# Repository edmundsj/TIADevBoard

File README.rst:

+/-5V TIA Dev Board
=========================

Features
----------
- On-board +/-5V supply generation
- Uses a low-noise opamp: ADA4622 (<1fA/rtHz, <15nV/rtHz)
- Low bias current opamp (<10pA) for accurate DC current measurement
- Opamp is unity gain stable, no input offset (<2uV), common-mode input beyond the rails, R2R output
- SMA input and output
- Low parasitic input/output capacitance

Issues in Versions 1,2
-----------------------
- [FIXED in v3] Old versions of this PCB relied on an off-board +/-15V dual supply, which was coupling in a huge amount of noise into the opamp.
- [FIXED in v3] Old opamp (ADA4625) appears to be often out of stock and is quite expensive (~$10). 

Issues in Version 3
--------------------
- The screw terminal is exerting force on an unspported area of the PCB, I should add another couple of standoffs so this does not happen.
- The -5V input is actually -7.5V. Should use two 3k resistors instead of two 1k resistors
- [FIXED v4] Pin 2 (sense pin) on ADP7183 is not connected to anything. It should be connected to Vout.
- [FIXED v4] There should be a 1uF capacitor to ground hanging off pin VA.
- [FIXED v4] There should be a 10nF capacitor between VA and VFB, not 1uF.

Issues in Version 4
---------------------
- [FIXED v5] Very high output noise (~10uV/rtHz) when driving diode with opamp. Switched to driving with GND.
- [FIXED v5] OPA2387 appears to have ~5x the specced current noise. Switched to ADA4622 (0.7fA/rtHz vs 70). 
- [FIXED v5] Switch back to dual supply with linear regulators
- [FIXED v5] Filter the output of the switched supply with an CLC network
- [FIXED v5] Add bulkhead-mount input/output SMA connectors to enclose entire board in grounded Faraday cage

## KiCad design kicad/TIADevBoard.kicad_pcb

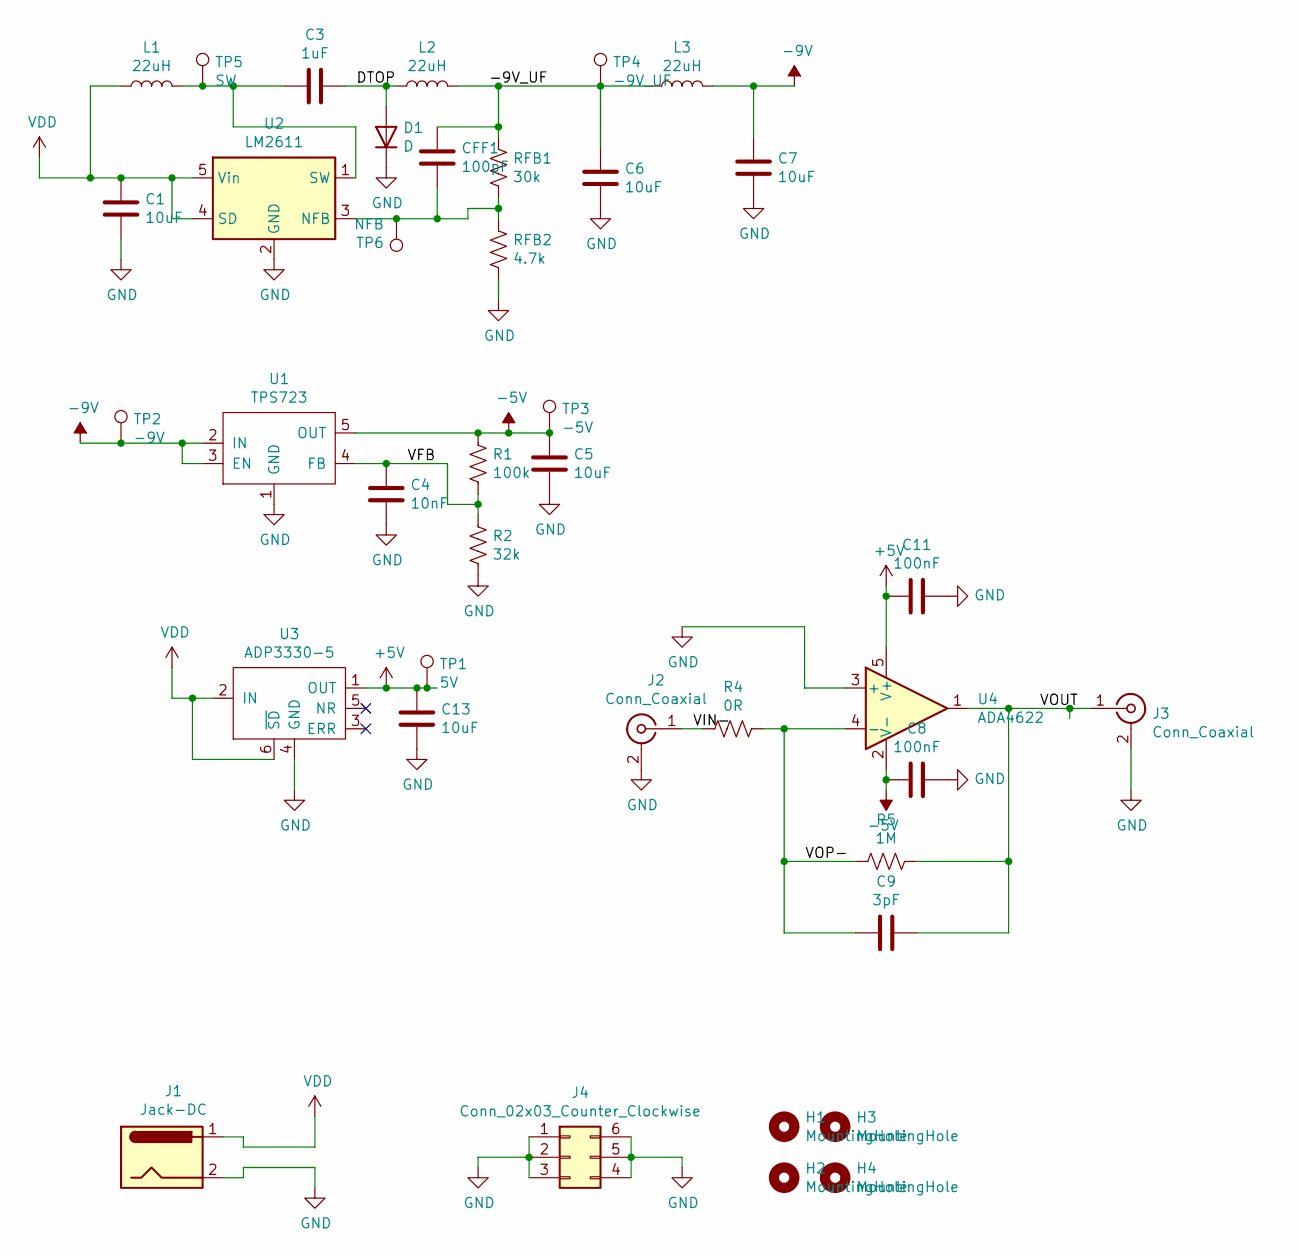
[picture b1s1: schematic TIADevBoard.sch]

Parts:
C1, C5, C6, C7, C13: 10uF; C_0805_2012Metric_Pad1.15x1.40mm_HandSolder
C3: 1uF; C_0805_2012Metric_Pad1.15x1.40mm_HandSolder
C4: 10nF; C_0805_2012Metric_Pad1.15x1.40mm_HandSolder
C8, C11: 100nF; C_0805_2012Metric_Pad1.15x1.40mm_HandSolder
C9: 3pF; C_0805_2012Metric_Pad1.15x1.40mm_HandSolder
CFF1: 100pF; C_0805_2012Metric_Pad1.15x1.40mm_HandSolder
D1: D; D_SOD-323_HandSoldering
H1, H2, H3, H4: MountingHole; m3_mounting_hole
J1: Jack-DC; BarrelJack_Horizontal
J2, J3: Conn_Coaxial; CON-SMA-EDGE-S
J4: Conn_02x03_Counter_Clockwise; PinHeader_2x03_P2.54mm_Vertical
L1, L2, L3: 22uH; L_0805_2012Metric_Pad1.15x1.40mm_HandSolder
R1: 100k; R_0805_2012Metric_Pad1.15x1.40mm_HandSolder
R2: 32k; R_0805_2012Metric_Pad1.15x1.40mm_HandSolder
R4: 0R; R_0805_2012Metric_Pad1.15x1.40mm_HandSolder
R5: 1M; R_0805_2012Metric_Pad1.15x1.40mm_HandSolder
RFB1: 30k; R_0805_2012Metric_Pad1.15x1.40mm_HandSolder
RFB2: 4.7k; R_0805_2012Metric_Pad1.15x1.40mm_HandSolder
TP1: 5V; TestPoint_Keystone_5000-5004_Miniature
TP2: -9V; TestPoint_Keystone_5000-5004_Miniature
TP3: -5V; TestPoint_Keystone_5000-5004_Miniature
TP4: -9V_UF; TestPoint_Keystone_5000-5004_Miniature
TP5: SW; TestPoint_Keystone_5000-5004_Miniature
TP6: NFB; TestPoint_Keystone_5000-5004_Miniature
U1: TPS723; SOT-23-5_HandSoldering
U2: LM2611; SOT-23-5_HandSoldering
U3: ADP3330-5; SOT-23-6_Handsoldering
U4: ADA4622; SOT-23-5_HandSoldering

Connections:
+5V: C11.2, C13.1, TP1.1, U3.1 (OUT), U4.5 (V+)
-5V: C5.1, C8.2, R1.1, TP3.1, U1.5 (OUT), U4.2 (V-)
-9V: C7.1, L3.2, TP2.1, U1.2 (IN), U1.3 (EN)
/-9V_UF: C6.1, CFF1.1, L2.2, L3.1, RFB1.1, TP4.1
/DTOP: C3.1, D1.2 (A), L2.1
/VFB: C4.1, R1.2, R2.1, U1.4 (FB)
/VIN-: J2.1 (In), R4.2
/VOP-: C9.2, R4.1, R5.2, U4.4 (-)
/VOUT: C9.1, J3.1 (In), R5.1, U4.1
GND: C1.2, C4.2, C5.2, C6.2, C7.2, C8.1, C11.1, C13.2, D1.1 (K), J1.2, J2.2 (Ext), J3.2 (Ext), J4.1, J4.2, J4.3, J4.4, J4.5, J4.6, R2.2, RFB2.2, U1.1 (GND), U2.2 (GND), U3.4 (GND), U4.3 (+)
unnamed: C3.2, L1.2, TP5.1, U2.1 (SW)
unnamed: CFF1.2, RFB1.2, RFB2.1, TP6.1, U2.3 (NFB)
VDD: C1.1, J1.1, L1.1, U2.4 (SD), U2.5 (Vin), U3.2 (IN), U3.6 (~SD)

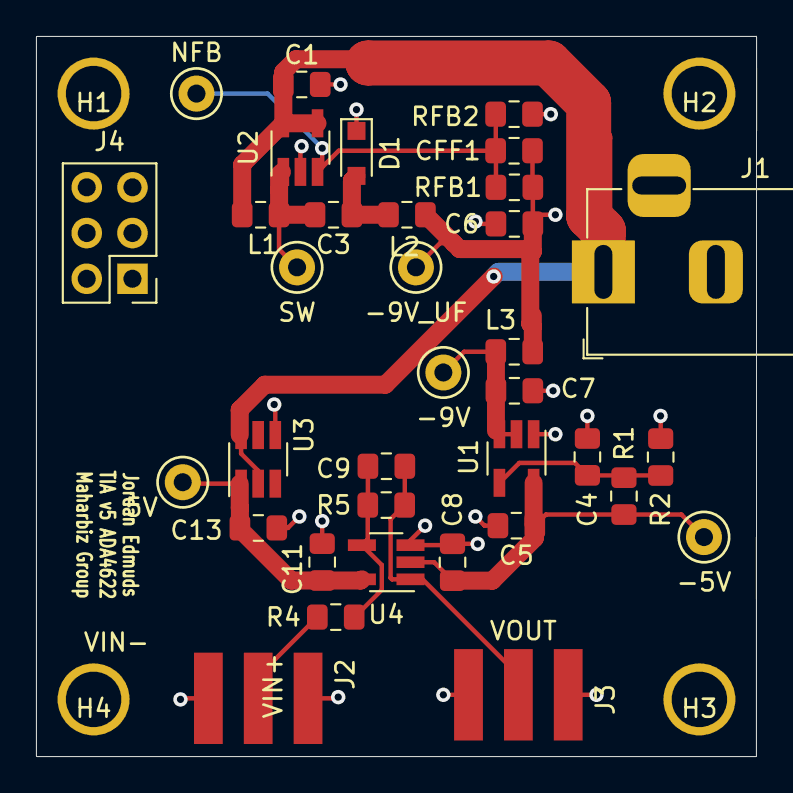
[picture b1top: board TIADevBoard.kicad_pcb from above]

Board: 2 copper layers, 40.0 x 40.0 mm, 39 parts (0 on the bottom side), 13 nets.

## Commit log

2021-01-15 added schematic, PCB not routed or laid out. BOM not complete
2021-01-15 Version 3 complete with +3V/-2.5V low noise LDO regulated supplies, a -5V inverting DC switching converter, and a new low-noise TIA
2021-01-15 added bill of materials, README
2021-01-29 added second SMA connector for Vin+ terminal
2021-01-29 added 3D image of TIA dev board
2021-02-09 fixed some errors in version 3 of PCB, updated the README to that effect.
2021-02-09 partial redesign of TIA v4, removed boost/buck converter, -2.5V linear regulator, added in second opamp in unity gain configuration with bias voltage. Layout not complete.
2021-02-12 modified TIA dev board to use a single supply of 3.3V, and optionally bias both sides of the diode at VDD/2 using one of the opamps to drive the guard shield. Should work just as well as grounding it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
2021-02-18 updated PCB layout to incorporate schematic changes
2021-02-25 updated README with debugging results from version 3
2021-02-25 added gerbers for version 5
2021-03-12 updated dev board schematic with correct resistor values
2021-05-10 updated BOM with new components, moved kicad parts into their own folder
2021-05-10 updated PNG to latest dev board file
2021-05-10 updated README w/ new opamp
